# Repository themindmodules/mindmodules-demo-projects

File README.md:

# MindModules Demo Projects

Five complete example projects from [@themindmodules](https://instagram.com/themindmodules): PCB design,
STM32, Arduino, core electronics, a hobby build and a hackathon kit. Each folder is a self-contained project
with its own README, documentation, design files and BOM.

| # | Project | Type | What is inside |
|---|---|---|---|
| 01 | [stm32-adc-dma-datalogger](01-stm32-adc-dma-datalogger) | STM32 firmware | 4-channel ADC + DMA logger, CubeMX settings, timing maths, test plan |
| 02 | [arduino-plant-monitor](02-arduino-plant-monitor) | Arduino | Soil moisture + safe auto-watering, wiring, calibration, safety notes |
| 03 | [lm317-adjustable-supply](03-lm317-adjustable-supply) | **PCB** | KiCad schematic + PCB, gerbers, BOM, assembly and ordering guide |
| 04 | [nano-rgb-led-controller](04-nano-rgb-led-controller) | Hobby / mixed | 12 V RGB strip controller: schematic, perfboard guide, firmware |
| 05 | [hackathon-gridwatch](05-hackathon-gridwatch) | Hackathon | Energy anomaly detection demo, pitch, judge Q&A, 24 h plan |
| 06 | [stm32-rtc-low-power-logger](06-stm32-rtc-low-power-logger) | STM32 firmware | Stop 2 + RTC wake-up loop, VREFINT supply and temp maths, ring buffer, current budget model |
| 07 | [hobby-cable-tester](07-hobby-cable-tester) | Hobby / mixed | 8-wire tester with 595/165 scan: schematic, perfboard wiring table, firmware with testable logic |
| 08 | [pcb-lifepo4-4s-bms](08-pcb-lifepo4-4s-bms) | PCB | KiCad schematic and PCB, gerbers, TL431 balancer, LM393 cutoff, design notes, test plan. Topic suggested by Sujan Ghosh |
| 09 | [stm32-i2c-sensor-logger](09-stm32-i2c-sensor-logger) | STM32 firmware | Bus scan with device hints, LM75/TMP102 CSV logger, CubeMX settings, pull-up maths, test plan |
| 10 | [pcb-transistor-relay-driver](10-pcb-transistor-relay-driver) | PCB | BC337 low side relay drivers with flyback diodes and LEDs, base resistor maths, KiCad schematic, routed PCB and gerbers |
| 11 | [stm32-pwm-motor-speed-controller](11-stm32-pwm-motor-speed-controller) | STM32 firmware | STM32F411 + DRV8871, encoder on TIM2, 100 Hz PI loop with anti-windup, live tuning over UART, loop simulator |
| 12 | [hack-attendance-qr](12-hack-attendance-qr) | Hackathon | Rotating QR token, scan simulator, proxy and duplicate rules, self-test, dashboard, pitch and judge Q&A |

## Status

These are reference designs. The KiCad files pass ERC/DRC and the code compiles, but **no board here has been
fabricated or bench-tested**, and the hackathon demo runs on simulated data. Every README says exactly what was
and was not verified. Follow the test plans before trusting any design, and take care with anything that touches mains voltage.

## Want more?

Exclusive PCB designs, STM32 and Arduino projects, documentation, personal guidance, Q&A and doubt calls are
available to Inner Circle subscribers on Instagram: [@themindmodules](https://instagram.com/themindmodules).

## License

See `LICENSE.md` inside each project.

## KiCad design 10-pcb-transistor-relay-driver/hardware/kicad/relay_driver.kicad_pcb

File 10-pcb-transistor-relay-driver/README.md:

# Two Channel Transistor Relay Driver (5 V coil)

A small through-hole board that lets a microcontroller pin switch a 5 V relay. Each channel uses
an NPN transistor as a low side switch, a base resistor sized for both 5 V and 3.3 V logic,
a pull-down so the relay stays off while the controller boots, a flyback diode across the coil
and an LED that shows when the coil is powered. Two identical channels sit side by side.

> **Status:** the schematic passes KiCad ERC (0 issues) and the PCB passes DRC (0 violations,
> 0 unconnected). The exported netlist was checked against the intended connections, net by net.
> All component values come from hand calculations in `docs/design-notes.md`. The circuit was
> **not simulated** and the board has **not been built or tested on a bench yet**. Treat the first
> build as a prototype and follow `docs/assembly-and-test.md`.

## What it does

| Block | Parts per channel | Value |
|---|---|---|
| Switch | BC337 NPN in TO-92 | coil current about 71 mA, transistor fully saturated |
| Base drive | 470 ohm series resistor | about 8.9 mA from a 5 V pin, about 5.2 mA from a 3.3 V pin |
| Off by default | 10k base pull-down | relay stays off while the input floats |
| Coil protection | 1N4148 across the coil | collector clamps near 5.8 V when the coil turns off |
| Indicator | red LED with 1k | about 3 mA, lights while the coil is on |

## At a glance

| Item | Value |
|---|---|
| Coil supply | 5 V DC, about 150 mA with both relays on |
| Logic input | 3.3 V or 5 V, active high, about 5 to 9 mA per input |
| Relay | SRD-05VDC-SL-C (SPDT, COM, NC and NO brought out) |
| Contact limit on this board | **24 V DC, 3 A**. Low voltage only, never mains |
| Board | 64 x 76 mm, 2 layers, all through-hole, two M3 holes |
| Tools | KiCad 10 (project files included) |

## Connectors

| Connector | Pins |
|---|---|
| J3 screw terminal | +5V, GND (coil supply) |
| J4 pin header | 5V, IN1, IN2, GND (to the microcontroller) |
| J1, J2 screw terminals | COM, NC, NO for relay 1 and relay 2 |

The 5V pin on J4 is the same net as J3. Power the board from one of them, not two different supplies.

## Folder map

| Path | Contents |
|---|---|
| `hardware/kicad/` | KiCad project: `.kicad_pro`, `.kicad_sch`, `.kicad_pcb` |
| `hardware/gerbers/` | Gerbers, drill file and placement file |
| `hardware/docs/` | Schematic PDF, PCB PDF and SVG, top layer preview |
| `hardware/reports/` | DRC, ERC and netlist reports |
| `bom/bom.csv` | Bill of materials |
| `docs/design-notes.md` | How the driver works, every formula and why each value was picked |
| `docs/assembly-and-test.md` | Build order, test plan and a short example sketch |
| `docs/ordering-gerbers.md` | How to order the PCB |
| `tools/` | Python scripts that generate the schematic and PCB (rebuild with KiCad's Python) |

## Quick start

1. Read `docs/design-notes.md` so you know why the values are what they are.
2. Order the PCB from the files in `hardware/gerbers/` (see `docs/ordering-gerbers.md`) and buy the parts in `bom/bom.csv`.
3. Build and check it with `docs/assembly-and-test.md`. Test with a current limited 5 V supply first.

## Rebuild the design files

```sh
"<KiCad>/bin/python.exe" tools/build_relay.py <path-to-this-project>
sh tools/export.sh <path-to-this-project> relay_driver     # needs kicad-cli
```

`tools/router.py` is a small grid router that lays the signal tracks. The relay contact tracks are
placed by hand at 1.5 mm width.

## License

Personal and educational use for MindModules Inner Circle subscribers. See `LICENSE.md`.

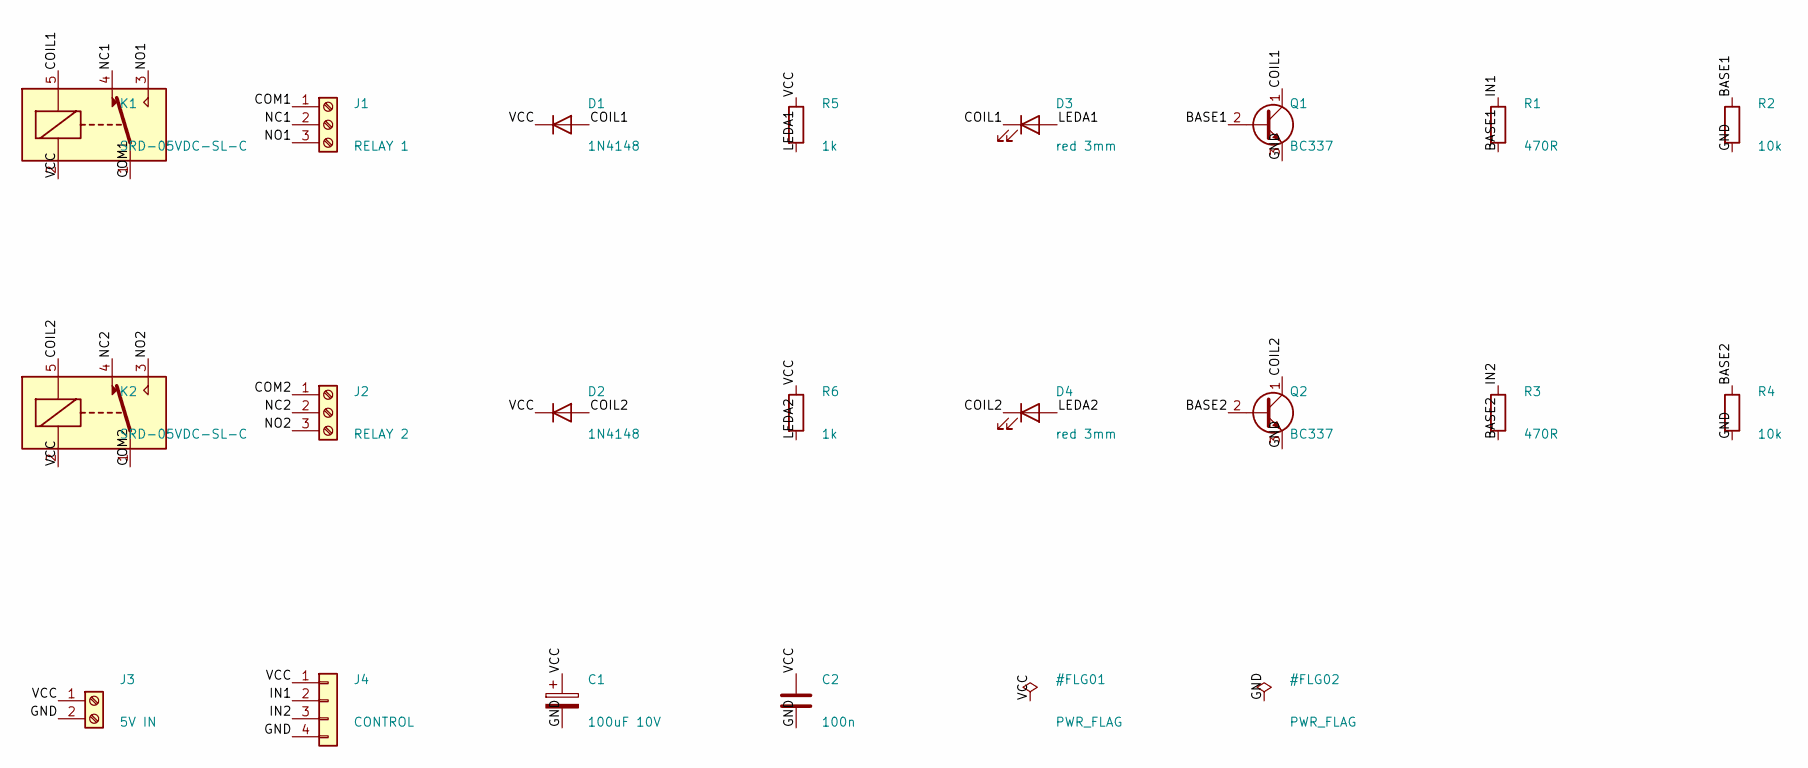
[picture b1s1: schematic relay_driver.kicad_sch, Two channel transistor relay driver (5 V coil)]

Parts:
C1: 100uF 10V; CP_Radial_D6.3mm_P2.50mm
C2: 100n; C_Disc_D5.0mm_W2.5mm_P5.00mm
D1, D2: 1N4148; D_DO-35_SOD27_P7.62mm_Horizontal
D3, D4: red 3mm; LED_D3.0mm
J1: RELAY 1; TerminalBlock_Phoenix_MKDS-1,5-3-5.08_1x03_P5.08mm_Horizont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
J2: RELAY 2; TerminalBlock_Phoenix_MKDS-1,5-3-5.08_1x03_P5.08mm_Horizont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
J3: 5V IN; TerminalBlock_Phoenix_MKDS-1,5-2-5.08_1x02_P5.08mm_Horizont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
J4: CONTROL; PinHeader_1x04_P2.54mm_Vertical
K1, K2: SRD-05VDC-SL-C; Relay_SPDT_SANYOU_SRD_Series_Form_C
Q1, Q2: BC337; TO-92_Inline_Wide
R1, R3: 470R; R_Axial_DIN0207_L6.3mm_D2.5mm_P7.62mm_Horizontal
R2, R4: 10k; R_Axial_DIN0207_L6.3mm_D2.5mm_P7.62mm_Horizontal
R5, R6: 1k; R_Axial_DIN0207_L6.3mm_D2.5mm_P7.62mm_Horizontal

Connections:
BASE1: Q1.2 (B), R1.2, R2.1
BASE2: Q2.2 (B), R3.2, R4.1
COIL1: D1.2 (A), D3.1 (K), K1.5, Q1.1 (C)
COIL2: D2.2 (A), D4.1 (K), K2.5, Q2.1 (C)
COM1: J1.1, K1.1
COM2: J2.1, K2.1
GND: C1.2, C2.2, J3.2, J4.4, Q1.3 (E), Q2.3 (E), R2.2, R4.2
IN1: J4.2, R1.1
IN2: J4.3, R3.1
LEDA1: D3.2 (A), R5.2
LEDA2: D4.2 (A), R6.2
NC1: J1.2, K1.4
NC2: J2.2, K2.4
NO1: J1.3, K1.3
NO2: J2.3, K2.3
VCC: C1.1, C2.1, D1.1 (K), D2.1 (K), J3.1, J4.1, K1.2, K2.2, R5.1, R6.1

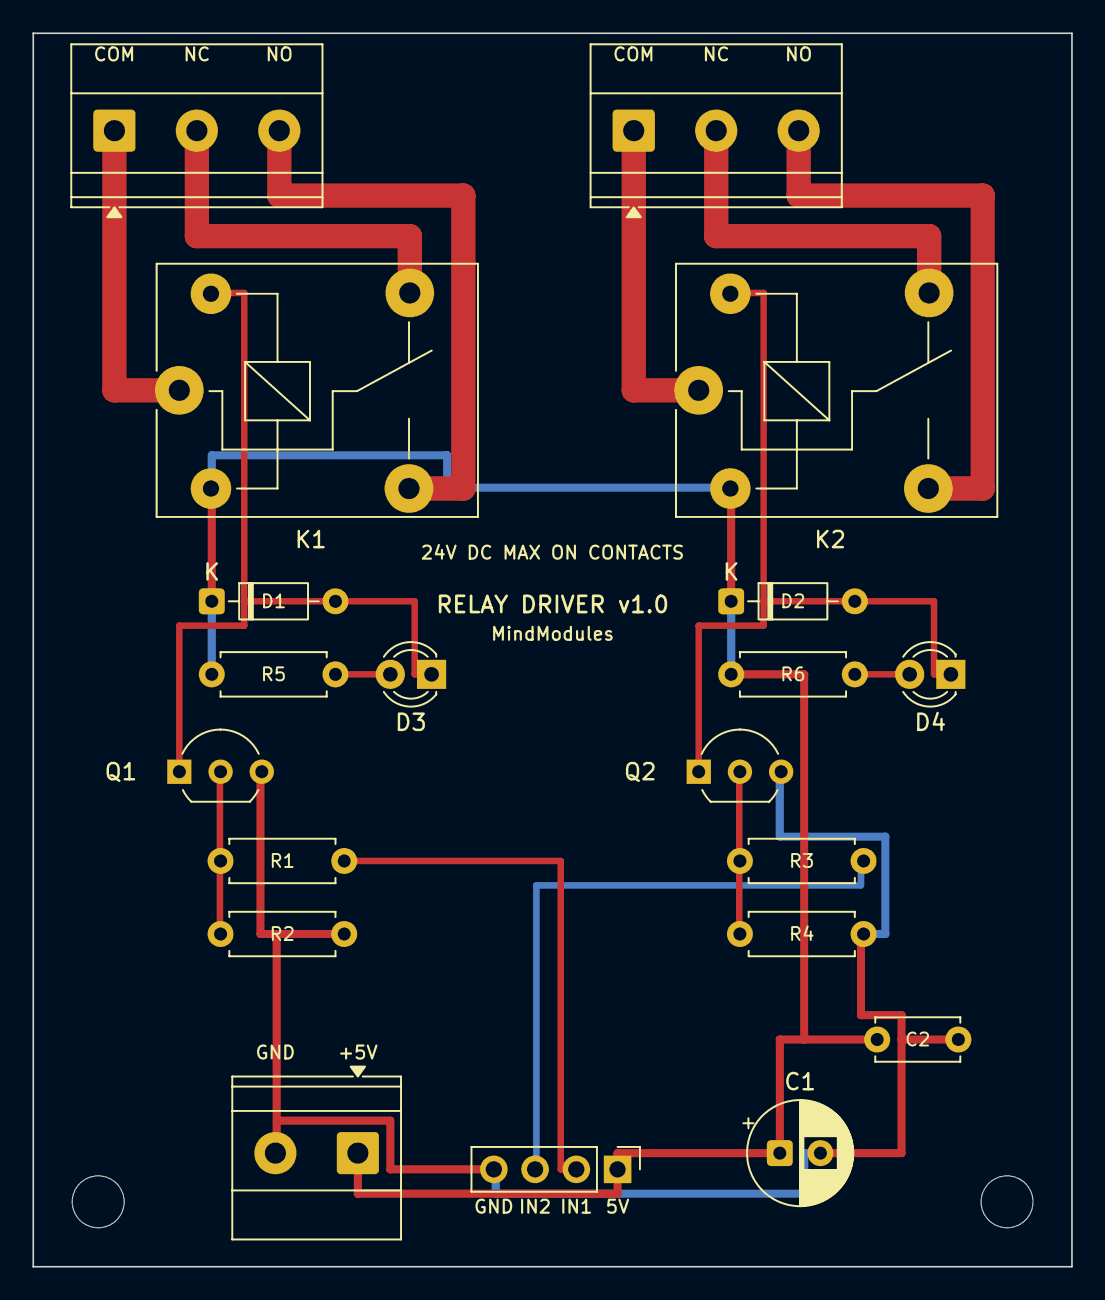
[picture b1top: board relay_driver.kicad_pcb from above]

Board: 2 copper layers, 64.0 x 76.0 mm, 22 parts (0 on the bottom side), 16 nets.

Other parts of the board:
H: MountingHole_3.2mm_M3
H#2: MountingHole_3.2mm_M3

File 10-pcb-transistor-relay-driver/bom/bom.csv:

"Refs","Value","Footprint","Qty","DNP"
"C1","100uF 10V","Capacitor_THT:CP_Radial_D6.3mm_P2.50mm","1",""
"C2","100n","Capacitor_THT:C_Disc_D5.0mm_W2.5mm_P5.00mm","1",""
"D1","1N4148","Diode_THT:D_DO-35_SOD27_P7.62mm_Horizontal","1",""
"D2","1N4148","Diode_THT:D_DO-35_SOD27_P7.62mm_Horizontal","1",""
"D3","red 3mm","LED_THT:LED_D3.0mm","1",""
"D4","red 3mm","LED_THT:LED_D3.0mm","1",""
"J1","RELAY 1","TerminalBlock_Phoenix:TerminalBlock_Phoenix_MKDS-1,5-3-5.08_1x03_P5.08mm_Horizontal","1",""
"J2","RELAY 2","TerminalBlock_Phoenix:TerminalBlock_Phoenix_MKDS-1,5-3-5.08_1x03_P5.08mm_Horizontal","1",""
"J3","5V IN","TerminalBlock_Phoenix:TerminalBlock_Phoenix_MKDS-1,5-2-5.08_1x02_P5.08mm_Horizontal","1",""
"J4","CONTROL","Connector_PinHeader_2.54mm:PinHeader_1x04_P2.54mm_Vertical","1",""
"K1","SRD-05VDC-SL-C","Relay_THT:Relay_SPDT_SANYOU_SRD_Series_Form_C","1",""
"K2","SRD-05VDC-SL-C","Relay_THT:Relay_SPDT_SANYOU_SRD_Series_Form_C","1",""
"Q1","BC337","Package_TO_SOT_THT:TO-92_Inline_Wide","1",""
"Q2","BC337","Package_TO_SOT_THT:TO-92_Inline_Wide","1",""
"R1","470R","Resistor_THT:R_Axial_DIN0207_L6.3mm_D2.5mm_P7.62mm_Horizontal","1",""
"R2","10k","Resistor_THT:R_Axial_DIN0207_L6.3mm_D2.5mm_P7.62mm_Horizontal","1",""
"R3","470R","Resistor_THT:R_Axial_DIN0207_L6.3mm_D2.5mm_P7.62mm_Horizontal","1",""
"R4","10k","Resistor_THT:R_Axial_DIN0207_L6.3mm_D2.5mm_P7.62mm_Horizontal","1",""
"R5","1k","Resistor_THT:R_Axial_DIN0207_L6.3mm_D2.5mm_P7.62mm_Horizontal","1",""
"R6","1k","Resistor_THT:R_Axial_DIN0207_L6.3mm_D2.5mm_P7.62mm_Horizontal","1",""

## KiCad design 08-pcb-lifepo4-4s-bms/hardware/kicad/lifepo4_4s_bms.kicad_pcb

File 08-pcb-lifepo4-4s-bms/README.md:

# 4S LiFePO4 BMS: Cell Balancer and Load Protection Board

A through-hole battery management board for a 4 cell LiFePO4 pack (also called LFP or IFP cells,
12.8 V nominal, 14.6 V full). It does two jobs: it balances each cell at the top of charge, and it
disconnects the load on pack under-voltage and on over-current.

**Topic suggested by Sujan Ghosh** on the @themindmodules Instagram channel. Thanks Sujan.

> **Status:** the schematic passes KiCad ERC (0 issues) and the PCB passes DRC (0 violations,
> 0 unconnected), and the exported netlist matches the intended connections. All thresholds were
> calculated by hand and are listed in `docs/design-notes.md`. The circuit was **not simulated**
> and the board has **not been built or tested on a bench**. Treat the first build as a prototype,
> and read `docs/limits-and-safety.md` before connecting a real battery.

## What it does

| Function | How | Value |
|---|---|---|
| Cell balancing | One TL431 shunt per cell, starts bleeding through an 18 ohm resistor | starts at 3.60 V per cell, about 60 to 85 mA |
| Pack under-voltage cutoff | LM393 comparator watches the pack voltage and switches off a logic-level MOSFET | cuts at about 11.04 V (2.76 V per cell), reconnects at about 11.21 V |
| Over-current cutoff | 20 milliohm shunt, second comparator | trips at about 10 A |
| Load switch | IRLZ44N in the negative (low side) line | charging still flows through its body diode |

## What it does not do

It has no over-charge disconnect and no per cell under-voltage cutoff. It needs a proper
CC/CV LiFePO4 charger set to 14.4 V. The full list is in `docs/limits-and-safety.md`.

## At a glance

| Item | Value |
|---|---|
| Cells | 4 in series, LiFePO4 only (not Li-ion, not lead acid) |
| Pack voltage | 10 V to 14.6 V |
| Continuous current | **5 A** (copper width and shunt power), trips at about 10 A |
| Board | 100 x 94 mm, 2 layers, through-hole, four M3 holes |
| Idle drain | roughly 2.6 mA from the whole pack, so do not store a pack on the board |
| Tools | KiCad 10 (project files included) |

## Folder map

| Path | Contents |
|---|---|
| `hardware/kicad/` | KiCad project: `.kicad_pro`, `.kicad_sch`, `.kicad_pcb` |
| `hardware/gerbers/` | Gerbers, drill file and placement file |
| `hardware/docs/` | Schematic PDF, PCB PDF and SVG, preview images |
| `hardware/reports/` | DRC, ERC and netlist reports |
| `bom/bom.csv` | Bill of materials |
| `docs/design-notes.md` | How each block works, every formula and threshold |
| `docs/limits-and-safety.md` | What the board cannot protect against, and LiFePO4 handling rules |
| `docs/assembly-and-test.md` | Build order and a bench test plan using a variable supply |
| `tools/` | Python scripts that generate the schematic and PCB (rebuild with KiCad's Python) |

## Quick start

1. Read `docs/limits-and-safety.md` first.
2. Read `docs/design-notes.md` so you know why the values are what they are.
3. Order the PCB from the files in `hardware/gerbers/` and buy the parts in `bom/bom.csv`.
4. Build and test with `docs/assembly-and-test.md`. Test on a bench supply before any real cells.

## Rebuild the design files

```sh
"<KiCad>/bin/python.exe" tools/build_bms.py <path-to-this-repo>
sh tools/export.sh <path-to-this-repo> lifepo4_4s_bms     # needs kicad-cli
```

`tools/router.py` is a small grid router used to lay the tracks. The power tracks (pack positive,
shunt, load return) are placed by hand at 2 mm width.

## License

Personal and educational use for MindModules Inner Circle subscribers. See `LICENSE.md`.

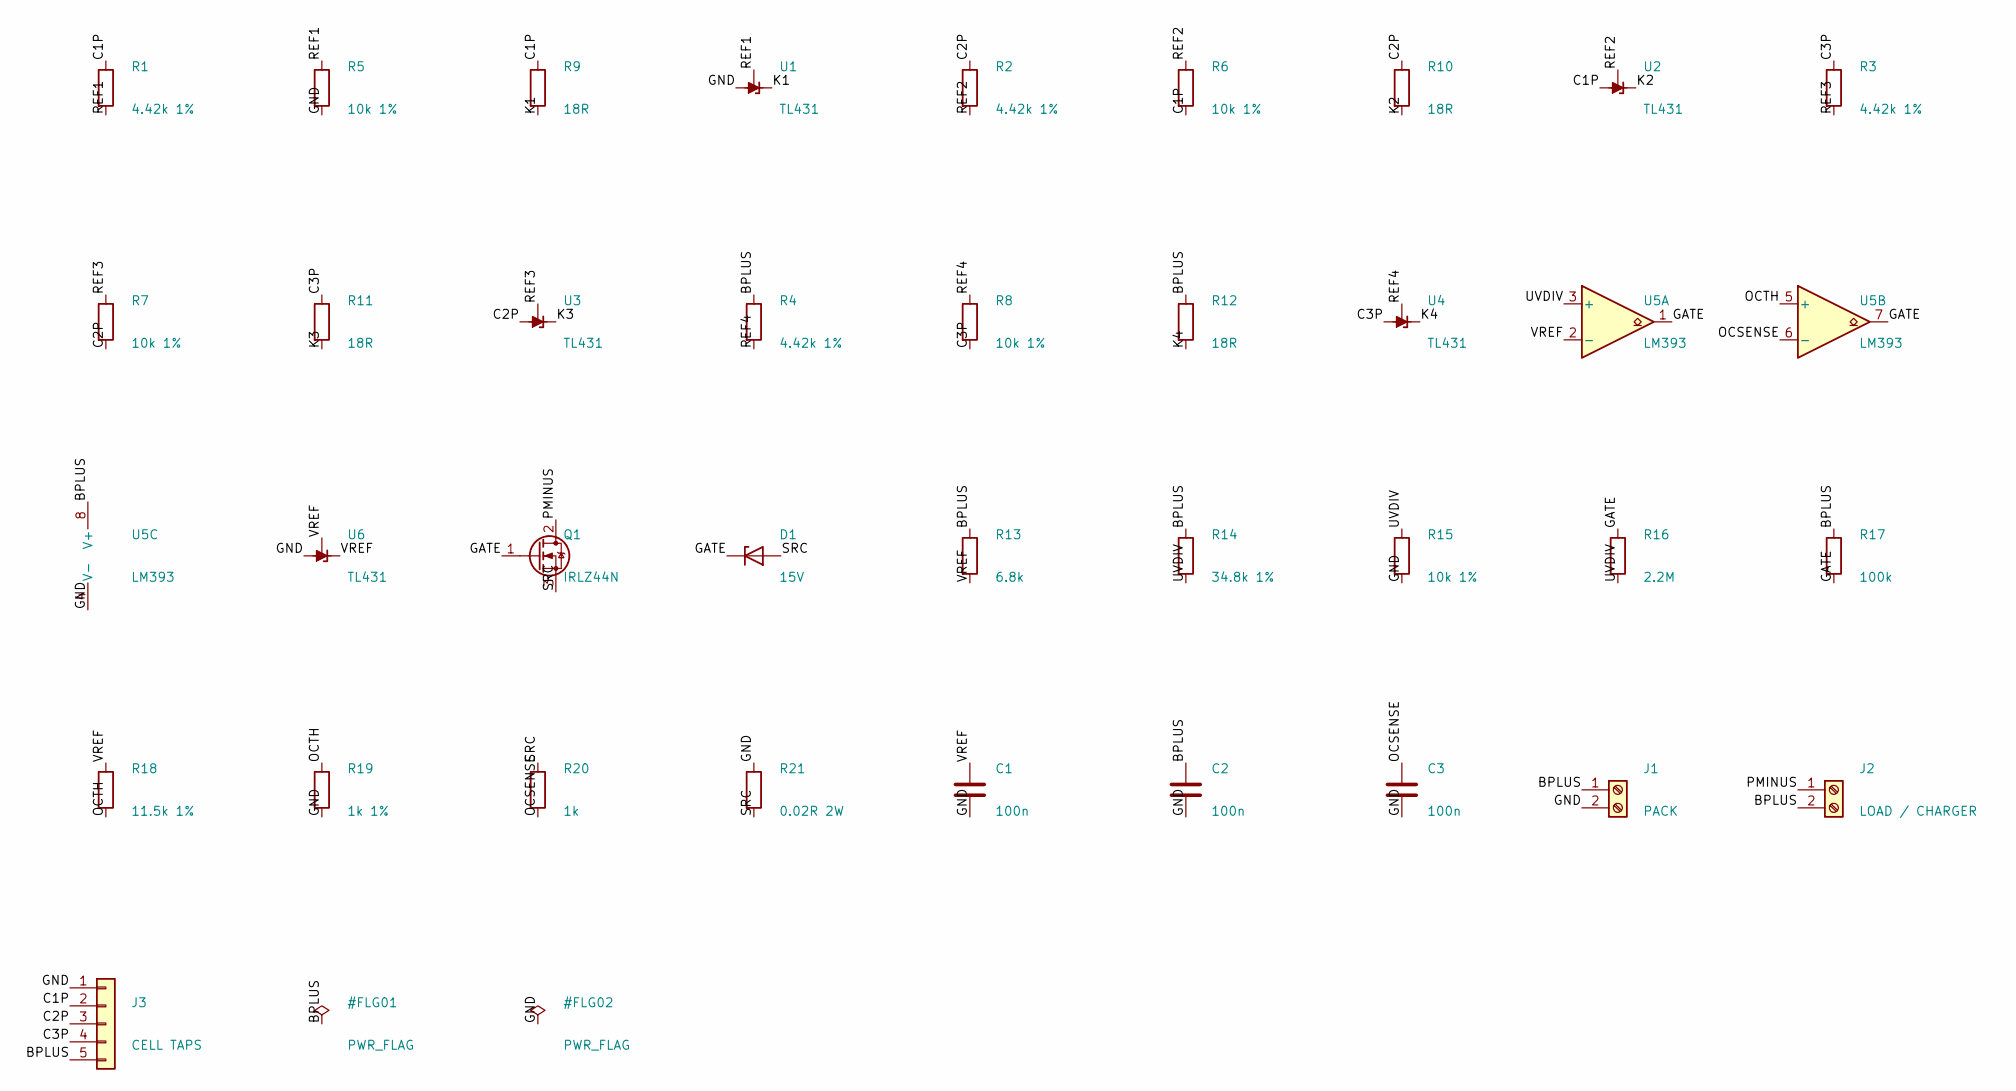
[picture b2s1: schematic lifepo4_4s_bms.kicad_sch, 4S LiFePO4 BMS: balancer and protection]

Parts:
C1, C2, C3: 100n; C_Disc_D5.0mm_W2.5mm_P5.00mm
D1: 15V; D_DO-41_SOD81_P10.16mm_Horizontal
J1: PACK; TerminalBlock_Phoenix_MKDS-1,5-2-5.08_1x02_P5.08mm_Horizont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
J2: LOAD / CHARGER; TerminalBlock_Phoenix_MKDS-1,5-2-5.08_1x02_P5.08mm_Horizont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
J3: CELL TAPS; PinHeader_1x05_P2.54mm_Vertical
Q1: IRLZ44N; TO-220-3_Vertical
R1, R2, R3, R4: 4.42k 1%; R_Axial_DIN0207_L6.3mm_D2.5mm_P7.62mm_Horizontal
R5, R6, R7, R8, R15: 10k 1%; R_Axial_DIN0207_L6.3mm_D2.5mm_P7.62mm_Horizontal
R9, R10, R11, R12: 18R; R_Axial_DIN0207_L6.3mm_D2.5mm_P7.62mm_Horizontal
R13: 6.8k; R_Axial_DIN0207_L6.3mm_D2.5mm_P7.62mm_Horizontal
R14: 34.8k 1%; R_Axial_DIN0207_L6.3mm_D2.5mm_P7.62mm_Horizontal
R16: 2.2M; R_Axial_DIN0207_L6.3mm_D2.5mm_P7.62mm_Horizontal
R17: 100k; R_Axial_DIN0207_L6.3mm_D2.5mm_P7.62mm_Horizontal
R18: 11.5k 1%; R_Axial_DIN0207_L6.3mm_D2.5mm_P7.62mm_Horizontal
R19: 1k 1%; R_Axial_DIN0207_L6.3mm_D2.5mm_P7.62mm_Horizontal
R20: 1k; R_Axial_DIN0207_L6.3mm_D2.5mm_P7.62mm_Horizontal
R21: 0.02R 2W; R_Axial_DIN0414_L11.9mm_D4.5mm_P15.24mm_Horizontal
U1, U2, U3, U4, U6: TL431; TO-92_Inline
U5: LM393; DIP-8_W7.62mm

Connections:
BPLUS: C2.1, J1.1, J2.2, J3.5, R4.1, R12.1, R13.1, R14.1, R17.1, U5.8 (V+)
C1P: J3.2, R1.1, R6.2, R9.1, U2.2 (A)
C2P: J3.3, R2.1, R7.2, R10.1, U3.2 (A)
C3P: J3.4, R3.1, R8.2, R11.1, U4.2 (A)
GATE: D1.1 (K), Q1.1 (G), R16.1, R17.2, U5.1, U5.7
GND: C1.2, C2.2, C3.2, J1.2, J3.1, R5.2, R15.2, R19.2, R21.1, U1.2 (A), U5.4 (V-), U6.2 (A)
K1: R9.2, U1.3 (K)
K2: R10.2, U2.3 (K)
K3: R11.2, U3.3 (K)
K4: R12.2, U4.3 (K)
OCSENSE: C3.1, R20.2, U5.6 (-)
OCTH: R18.2, R19.1, U5.5 (+)
PMINUS: J2.1, Q1.2 (D)
REF1: R1.2, R5.1, U1.1 (REF)
REF2: R2.2, R6.1, U2.1 (REF)
REF3: R3.2, R7.1, U3.1 (REF)
REF4: R4.2, R8.1, U4.1 (REF)
SRC: D1.2 (A), Q1.3 (S), R20.1, R21.2
UVDIV: R14.2, R15.1, R16.2, U5.3 (+)
VREF: C1.1, R13.2, R18.1, U5.2 (-), U6.1 (REF), U6.3 (K)

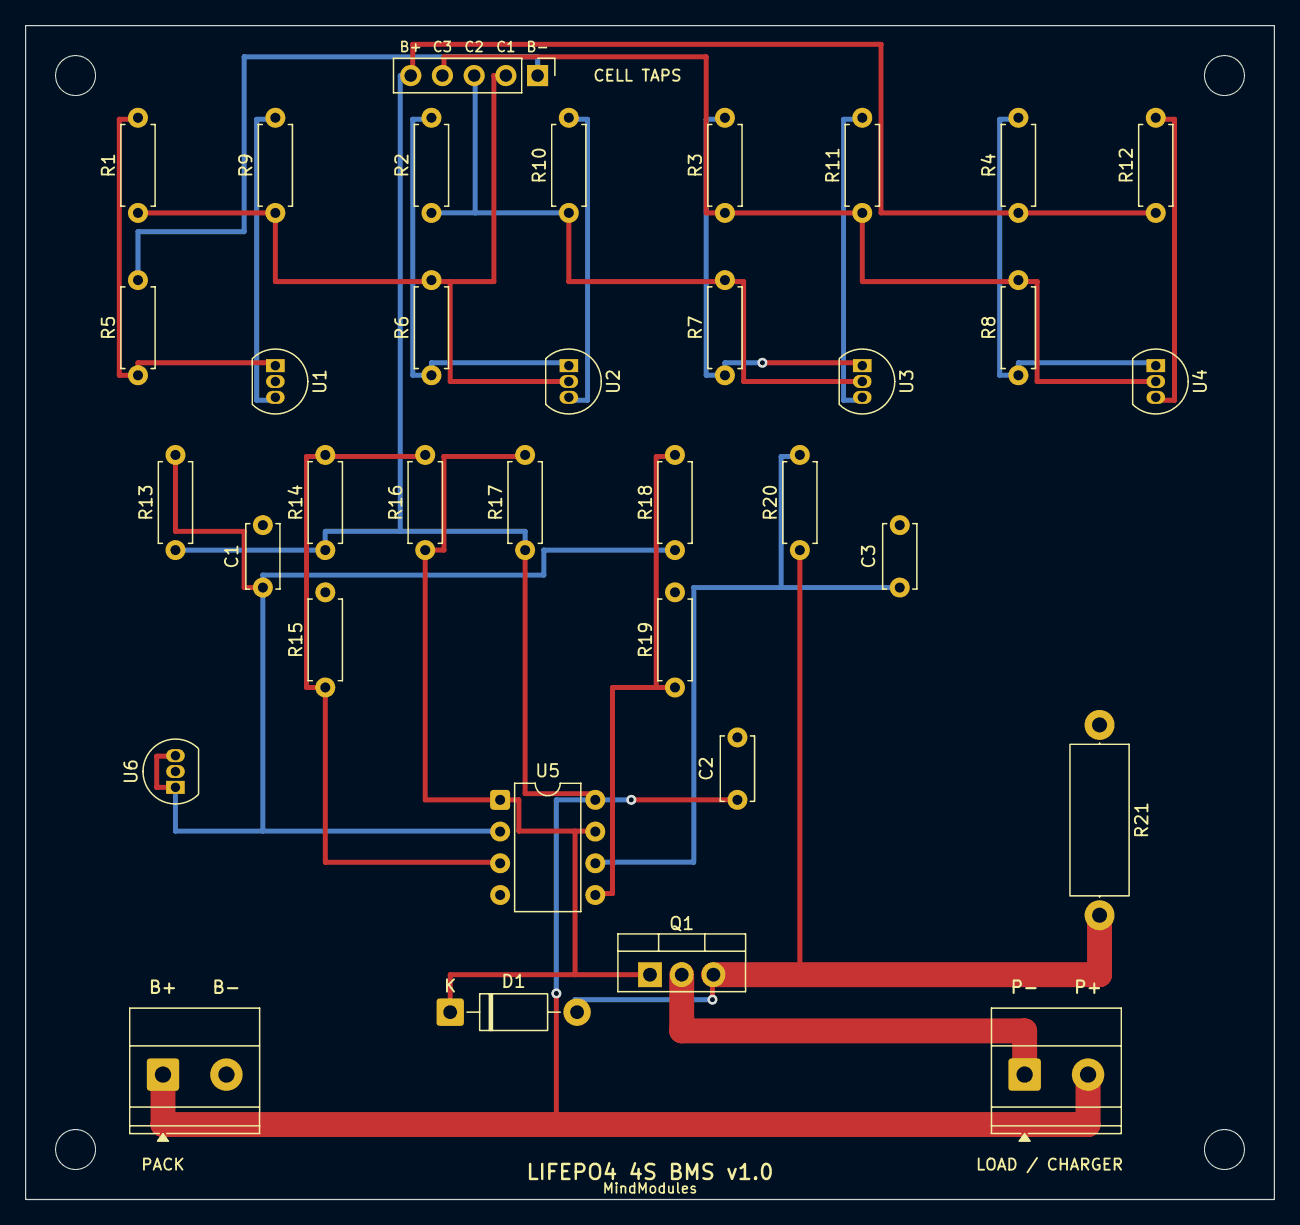
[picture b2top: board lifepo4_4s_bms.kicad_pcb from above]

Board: 2 copper layers, 100.0 x 94.0 mm, 39 parts (0 on the bottom side), 20 nets.

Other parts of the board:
H: MountingHole_3.2mm_M3
H#2, H#3, H#4: MountingHole_3.2mm_M3

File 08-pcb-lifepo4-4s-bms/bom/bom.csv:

"Refs","Value","Footprint","Qty","DNP"
"C1","100n","Capacitor_THT:C_Disc_D5.0mm_W2.5mm_P5.00mm","1",""
"C2","100n","Capacitor_THT:C_Disc_D5.0mm_W2.5mm_P5.00mm","1",""
"C3","100n","Capacitor_THT:C_Disc_D5.0mm_W2.5mm_P5.00mm","1",""
"D1","15V","Diode_THT:D_DO-41_SOD81_P10.16mm_Horizontal","1",""
"J1","PACK","TerminalBlock_Phoenix:TerminalBlock_Phoenix_MKDS-1,5-2-5.08_1x02_P5.08mm_Horizontal","1",""
"J2","LOAD / CHARGER","TerminalBlock_Phoenix:TerminalBlock_Phoenix_MKDS-1,5-2-5.08_1x02_P5.08mm_Horizontal","1",""
"J3","CELL TAPS","Connector_PinHeader_2.54mm:PinHeader_1x05_P2.54mm_Vertical","1",""
"Q1","IRLZ44N","Package_TO_SOT_THT:TO-220-3_Vertical","1",""
"R1","4.42k 1%","Resistor_THT:R_Axial_DIN0207_L6.3mm_D2.5mm_P7.62mm_Horizontal","1",""
"R2","4.42k 1%","Resistor_THT:R_Axial_DIN0207_L6.3mm_D2.5mm_P7.62mm_Horizontal","1",""
"R3","4.42k 1%","Resistor_THT:R_Axial_DIN0207_L6.3mm_D2.5mm_P7.62mm_Horizontal","1",""
"R4","4.42k 1%","Resistor_THT:R_Axial_DIN0207_L6.3mm_D2.5mm_P7.62mm_Horizontal","1",""
"R5","10k 1%","Resistor_THT:R_Axial_DIN0207_L6.3mm_D2.5mm_P7.62mm_Horizontal","1",""
"R6","10k 1%","Resistor_THT:R_Axial_DIN0207_L6.3mm_D2.5mm_P7.62mm_Horizontal","1",""
"R7","10k 1%","Resistor_THT:R_Axial_DIN0207_L6.3mm_D2.5mm_P7.62mm_Horizontal","1",""
"R8","10k 1%","Resistor_THT:R_Axial_DIN0207_L6.3mm_D2.5mm_P7.62mm_Horizontal","1",""
"R9","18R","Resistor_THT:R_Axial_DIN0207_L6.3mm_D2.5mm_P7.62mm_Horizontal","1",""
"R10","18R","Resistor_THT:R_Axial_DIN0207_L6.3mm_D2.5mm_P7.62mm_Horizontal","1",""
"R11","18R","Resistor_THT:R_Axial_DIN0207_L6.3mm_D2.5mm_P7.62mm_Horizontal","1",""
"R12","18R","Resistor_THT:R_Axial_DIN0207_L6.3mm_D2.5mm_P7.62mm_Horizontal","1",""
"R13","6.8k","Resistor_THT:R_Axial_DIN0207_L6.3mm_D2.5mm_P7.62mm_Horizontal","1",""
"R14","34.8k 1%","Resistor_THT:R_Axial_DIN0207_L6.3mm_D2.5mm_P7.62mm_Horizontal","1",""
"R15","10k 1%","Resistor_THT:R_Axial_DIN0207_L6.3mm_D2.5mm_P7.62mm_Horizontal","1",""
"R16","2.2M","Resistor_THT:R_Axial_DIN0207_L6.3mm_D2.5mm_P7.62mm_Horizontal","1",""
"R17","100k","Resistor_THT:R_Axial_DIN0207_L6.3mm_D2.5mm_P7.62mm_Horizontal","1",""
"R18","11.5k 1%","Resistor_THT:R_Axial_DIN0207_L6.3mm_D2.5mm_P7.62mm_Horizontal","1",""
"R19","1k 1%","Resistor_THT:R_Axial_DIN0207_L6.3mm_D2.5mm_P7.62mm_Horizontal","1",""
"R20","1k","Resistor_THT:R_Axial_DIN0207_L6.3mm_D2.5mm_P7.62mm_Horizontal","1",""
"R21","0.02R 2W","Resistor_THT:R_Axial_DIN0414_L11.9mm_D4.5mm_P15.24mm_Horizontal","1",""
"U1","TL431","Package_TO_SOT_THT:TO-92_Inline","1",""
"U2","TL431","Package_TO_SOT_THT:TO-92_Inline","1",""
"U3","TL431","Package_TO_SOT_THT:TO-92_Inline","1",""
"U4","TL431","Package_TO_SOT_THT:TO-92_Inline","1",""
"U5","LM393","Package_DIP:DIP-8_W7.62mm","1",""
"U6","TL431","Package_TO_SOT_THT:TO-92_Inline","1",""

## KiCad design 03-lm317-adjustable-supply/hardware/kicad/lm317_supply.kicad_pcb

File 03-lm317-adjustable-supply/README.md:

# LM317 Adjustable Bench Supply (1.25 V to about 11.8 V, up to 1 A)

A small through-hole linear regulator board: DC in (15-24 V), adjustable DC out with a trimmer.
It is the classic LM317 circuit done properly: input reverse-polarity diode, output-cap
discharge protection diode, and enough documentation to build, test and order it.

> **Status:** the schematic and PCB pass KiCad ERC (0 issues) and DRC (0 violations, 0 unconnected),
> and the exported netlist matches the intended connections. The board has **not** been fabricated
> or tested on a bench. Treat the first build as a prototype and follow `docs/assembly-and-test.md`,
> starting with a current-limited supply.

## At a glance

| Item | Value |
|---|---|
| Input | 15-24 V DC (needs at least Vout + about 3.2 V: 2.5 V regulator dropout + 0.7 V diode) |
| Output | 1.25 V to about 11.8 V, set by the trimmer |
| Max current | **1 A** (limited by D1, the 1N4007) and needs a heatsink at higher dissipation |
| Board | 66 x 38 mm, 2 layers, through-hole, two M3 holes |
| Tools | KiCad 10 (project files included) |

## Folder map

| Path | Contents |
|---|---|
| `hardware/kicad/` | KiCad project: `.kicad_pro`, `.kicad_sch`, `.kicad_pcb` |
| `hardware/gerbers/` | Gerbers + drill file, ready to upload to a PCB fab |
| `hardware/docs/` | Schematic PDF, PCB PDF and SVG, preview images |
| `hardware/reports/` | DRC, ERC and netlist reports |
| `bom/bom.csv` | Bill of materials |
| `docs/design-notes.md` | Formulas, thermal limits, why each part is there |
| `docs/assembly-and-test.md` | Build order and a test plan with expected readings |
| `docs/ordering-gerbers.md` | How to order the board |
| `tools/` | Python scripts that generated the schematic/PCB (rebuild with KiCad's Python) |

## Quick start

1. Read `docs/design-notes.md` (5 minutes) so you know the limits.
2. Order the PCB using `docs/ordering-gerbers.md`, buy parts from `bom/bom.csv`.
3. Build and test with `docs/assembly-and-test.md`.

## Rebuild the design files

```sh
"<KiCad>/bin/python.exe" tools/build_lm317.py <path-to-this-repo>
sh tools/export.sh <path-to-this-repo> lm317_supply     # needs kicad-cli
```

## License

Personal and educational use for MindModules Inner Circle subscribers. See `LICENSE.md`.

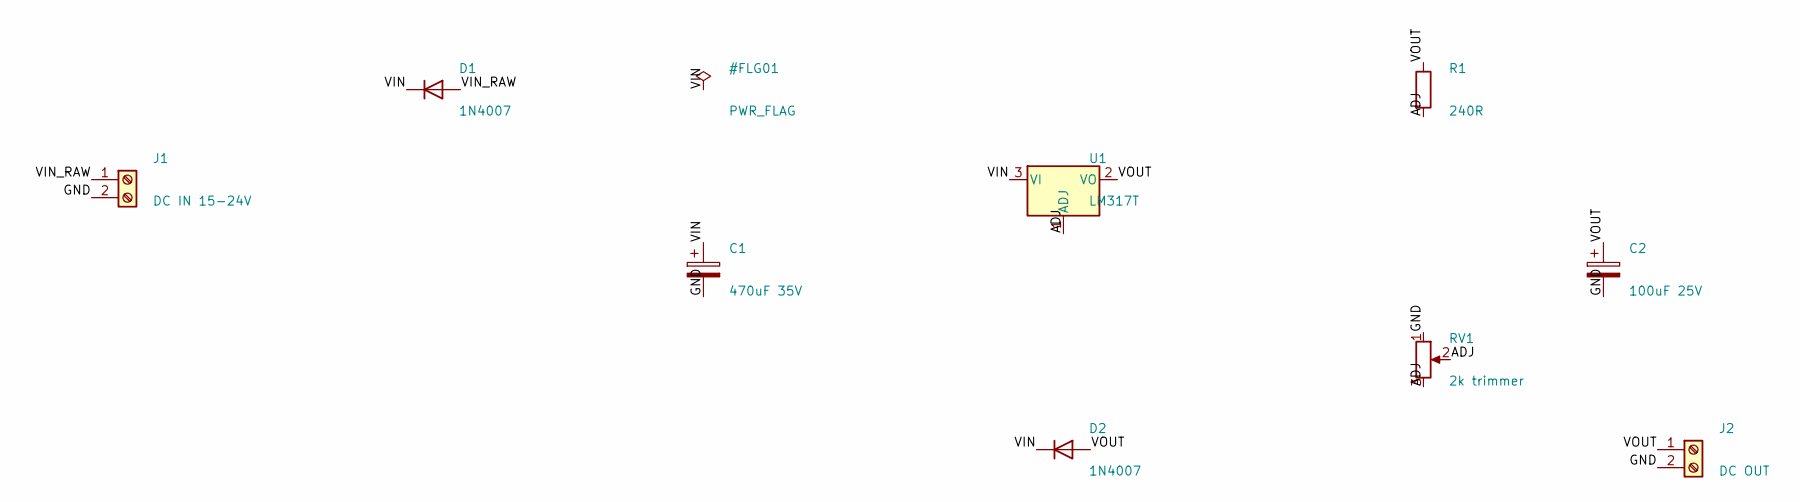
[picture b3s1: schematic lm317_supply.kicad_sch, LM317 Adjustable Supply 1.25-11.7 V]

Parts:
C1: 470uF 35V; CP_Radial_D8.0mm_P3.50mm
C2: 100uF 25V; CP_Radial_D6.3mm_P2.50mm
D1: 1N4007; D_DO-41_SOD81_P10.16mm_Horizontal
D2: 1N4007; D_DO-41_SOD81_P2.54mm_Vertical_CathodeUp
J1: DC IN 15-24V; TerminalBlock_Phoenix_MKDS-1,5-2-5.08_1x02_P5.08mm_Horizont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
J2: DC OUT; TerminalBlock_Phoenix_MKDS-1,5-2-5.08_1x02_P5.08mm_Horizont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
R1: 240R; R_Axial_DIN0207_L6.3mm_D2.5mm_P10.16mm_Horizontal
RV1: 2k trimmer; Potentiometer_Bourns_3296W_Vertical
U1: LM317T; TO-220-3_Vertical

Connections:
ADJ: R1.2, RV1.2, RV1.3, U1.1 (ADJ)
GND: C1.2, C2.2, J1.2, J2.2, RV1.1
VIN: C1.1, D1.1 (K), D2.1 (K), U1.3 (VI)
VIN_RAW: D1.2 (A), J1.1
VOUT: C2.1, D2.2 (A), J2.1, R1.1, U1.2 (VO)

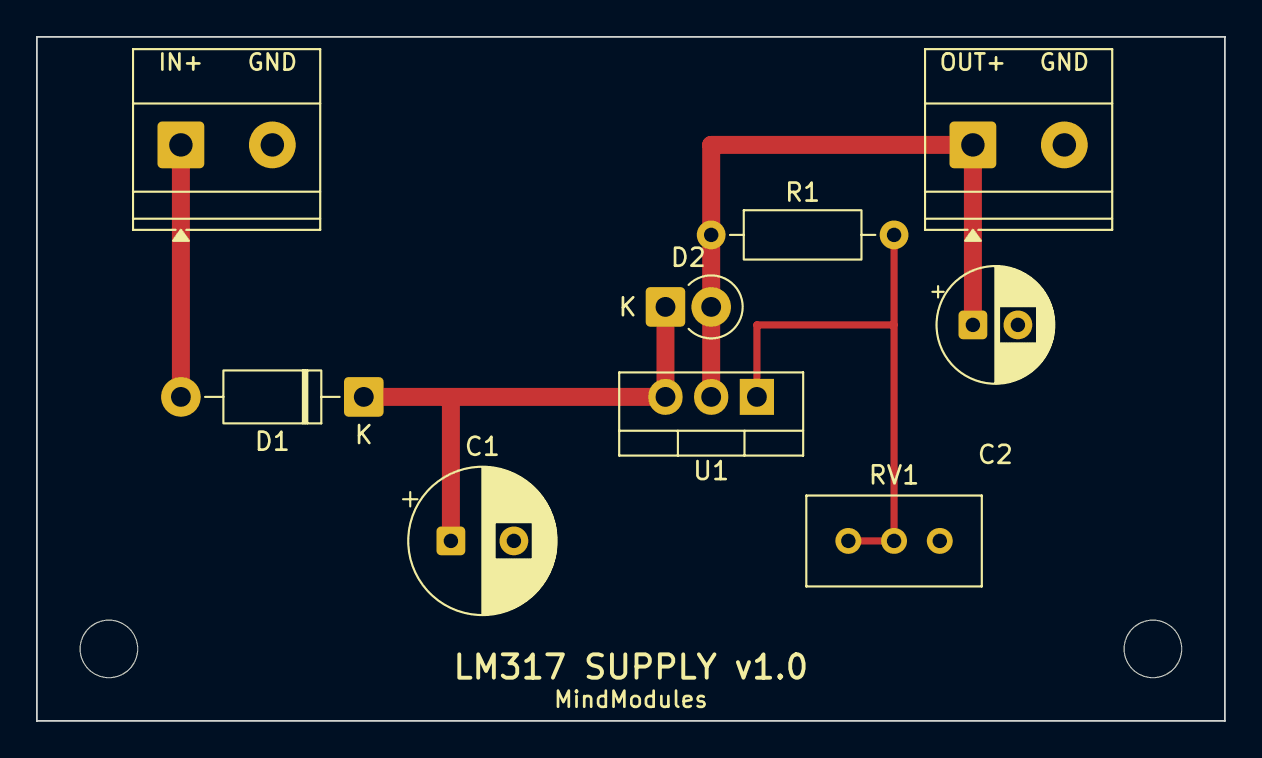
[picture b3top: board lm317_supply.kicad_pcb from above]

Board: 2 copper layers, 66.0 x 38.0 mm, 11 parts (0 on the bottom side), 5 nets.

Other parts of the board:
H: MountingHole_3.2mm_M3
H#2: MountingHole_3.2mm_M3

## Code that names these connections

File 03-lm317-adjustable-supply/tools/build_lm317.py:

"""Generate the LM317 adjustable supply: KiCad schematic + routed PCB.
Run with KiCad's bundled Python:  <KiCad>/bin/python.exe build_lm317.py <repo_root>
"""
import os
import sys

import pcbnew

sys.path.insert(0, os.path.dirname(os.path.abspath(__file__)))
import kigen

REPO = sys.argv[1]
NAME = "lm317_supply"
OUT = os.path.join(REPO, "hardware", "kicad")
os.makedirs(OUT, exist_ok=True)
FPLIB = r"D:\KICAD INSTALLATION\share\kicad\footprints"

TERM = "TerminalBlock_Phoenix:TerminalBlock_Phoenix_MKDS-1,5-2-5.08_1x02_P5.08mm_Horizontal"
TO220 = "Package_TO_SOT_THT:TO-220-3_Vertical"
D_H = "Diode_THT:D_DO-41_SOD81_P10.16mm_Horizontal"
D_V = "Diode_THT:D_DO-41_SOD81_P2.54mm_Vertical_CathodeUp"
CP8 = "Capacitor_THT:CP_Radial_D8.0mm_P3.50mm"
CP63 = "Capacitor_THT:CP_Radial_D6.3mm_P2.50mm"
R_H = "Resistor_THT:R_Axial_DIN0207_L6.3mm_D2.5mm_P10.16mm_Horizontal"
POT = "Potentiometer_THT:Potentiometer_Bourns_3296W_Vertical"

# ref, symbol, value, footprint, pin->net, schematic (x,y), pcb (x, y, rotation)
PARTS = [
    dict(ref="J1", lib="Connector:Screw_Terminal_01x02", value="DC IN 15-24V", fp=TERM,
         pins={"1": "VIN_RAW", "2": "GND"}, at=(45.72, 63.5), pcb=(8, 6, 0)),
    dict(ref="D1", lib="Device:D", value="1N4007", fp=D_H,
         pins={"1": "VIN", "2": "VIN_RAW"}, at=(88.9, 50.8), pcb=(18.16, 20, 180)),
    dict(ref="C1", lib="Device:C_Polarized", value="470uF 35V", fp=CP8,
         pins={"1": "VIN", "2": "GND"}, at=(127, 76.2), pcb=(23, 28, 0)),
    dict(ref="U1", lib="Regulator_Linear:LM317_TO-220", value="LM317T", fp=TO220,
         pins={"1": "ADJ", "2": "VOUT", "3": "VIN"}, at=(177.8, 63.5), pcb=(40, 20, 180)),
    dict(ref="D2", lib="Device:D", value="1N4007", fp=D_V,
         pins={"1": "VIN", "2": "VOUT"}, at=(177.8, 101.6), pcb=(34.92, 15, 0)),
    dict(ref="R1", lib="Device:R", value="240R", fp=R_H,
         pins={"1": "VOUT", "2": "ADJ"}, at=(228.6, 50.8), pcb=(37.46, 11, 0)),
    dict(ref="RV1", lib="Device:R_Potentiometer", value="2k trimmer", fp=POT,
         pins={"1": "GND", "2": "ADJ", "3": "ADJ"}, at=(228.6, 88.9), pcb=(50.16, 28, 0)),
    dict(ref="C2", lib="Device:C_Polarized", value="100uF 25V", fp=CP63,
         pins={"1": "VOUT", "2": "GND"}, at=(254, 76.2), pcb=(52, 16, 0)),
    dict(ref="J2", lib="Connector:Screw_Terminal_01x02", value="DC OUT", fp=TERM,
         pins={"1": "VOUT", "2": "GND"}, at=(266.7, 101.6), pcb=(52, 6, 0)),
    dict(ref="#FLG01", lib="power:PWR_FLAG", value="PWR_FLAG", fp="",
         pins={"1": "VIN"}, at=(127, 50.8), pcb=None),
]

# ---------------- schematic ----------------
kigen.generate_sch(os.path.join(OUT, NAME + ".kicad_sch"), NAME, "LM317 Adjustable Supply 1.25-11.7 V",
                   "A", PARTS, "Demo project for MindModules Inner Circle")
kigen.write_project(os.path.join(OUT, NAME + ".kicad_pro"), NAME)

# ---------------- PCB ----------------
OX, OY = 100.0, 80.0
W, H = 66.0, 38.0
FM = pcbnew.FromMM


def P(x, y):
    return pcbnew.VECTOR2I(FM(OX + x), FM(OY + y))


board = pcbnew.BOARD()
nets = {}
for n in sorted({v for p in PARTS for v in p["pins"].values()}):
    ni = pcbnew.NETINFO_ITEM(board, n)
    board.Add(ni)
    nets[n] = ni

origins = {}
for p in PARTS:
    if p["pcb"] is None:
        continue
    lib, name = p["fp"].split(":")
    fp = pcbnew.FootprintLoad(os.path.join(FPLIB, lib + ".pretty"), name)
    fp.SetReference(p["ref"])
    fp.SetValue(p["value"])
    x, y, rot = p["pcb"]
    fp.SetPosition(P(x, y))
    if rot:
        fp.SetOrientationDegrees(rot)
    for pad in fp.Pads():
        net = p["pins"].get(pad.GetNumber())
        if net:
            pad.SetNet(nets[net])
    fp.Value().SetVisible(False)
    if p["ref"] in ("J1", "J2"):
        fp.Reference().SetVisible(False)   # terminals are labelled by silk text instead
    if p["ref"] == "C2":
        fp.Reference().SetPosition(P(x + 1.25, y + 7.2))
    board.Add(fp)
    origins[p["ref"]] = fp


def pad(ref, num):
    for pd in origins[ref].Pads():
        if pd.GetNumber() == str(num):
            pos = pd.GetPosition()
            return (round(pcbnew.ToMM(pos.x) - OX, 3), round(pcbnew.ToMM(pos.y) - OY, 3))
    raise KeyError((ref, num))


def track(net, pts, w):
    for a, b in zip(pts, pts[1:]):
        t = pcbnew.PCB_TRACK(board)
        t.SetStart(P(*a))
        t.SetEnd(P(*b))
        t.SetWidth(FM(w))
        t.SetLayer(pcbnew.F_Cu)
        t.SetNet(nets[net])
        board.Add(t)


def line(a, b, layer, width):
    s = pcbnew.PCB_SHAPE(board)
    s.SetShape(pcbnew.SHAPE_T_SEGMENT)
    s.SetStart(P(*a))
    s.SetEnd(P(*b))
    s.SetLayer(layer)
    s.SetWidth(FM(width))
    board.Add(s)


# board outline
for a, b in [((0, 0), (W, 0)), ((W, 0), (W, H)), ((W, H), (0, H)), ((0, H), (0, 0))]:
    line(a, b, pcbnew.Edge_Cuts, 0.1)

# mounting holes
for hx, hy in [(4, H - 4), (W - 4, H - 4)]:
    mh = pcbnew.FootprintLoad(os.path.join(FPLIB, "MountingHole.pretty"), "MountingHole_3.2mm_M3")
    mh.SetReference("H")
    mh.Reference().SetVisible(False)
    mh.Value().SetVisible(False)
    mh.SetPosition(P(hx, hy))
    board.Add(mh)

# routing (all on F.Cu, GND is a pour on B.Cu)
PW, SG = 1.0, 0.4
track("VIN_RAW", [pad("J1", 1), pad("D1", 2)], PW)
track("VIN", [pad("D1", 1), pad("U1", 3)], PW)
track("VIN", [(23, 20), pad("C1", 1)], PW)
track("VIN", [pad("D2", 1), (pad("D2", 1)[0], 20)], PW)
track("VOUT", [pad("U1", 2), (pad("U1", 2)[0], 6), pad("J2", 1)], PW)
track("VOUT", [pad("J2", 1), pad("C2", 1)], PW)
adj_x = pad("R1", 2)[0]
track("ADJ", [pad("U1", 1), (pad("U1", 1)[0], 16), (adj_x, 16)], SG)
track("ADJ", [pad("R1", 2), (adj_x, 28), pad("RV1", 2)], SG)
track("ADJ", [pad("RV1", 2), pad("RV1", 3)], SG)

# GND pour on B.Cu
z = pcbnew.ZONE(board)
z.SetLayer(pcbnew.B_Cu)
z.SetNet(nets["GND"])
ol = z.Outline()
ol.NewOutline()
for cx, cy in [(0.5, 0.5), (W - 0.5, 0.5), (W - 0.5, H - 0.5), (0.5, H - 0.5)]:
    v = P(cx, cy)
    ol.Append(v.x, v.y)
z.SetMinThickness(FM(0.25))
z.SetLocalClearance(FM(0.4))
z.SetPadConnection(pcbnew.ZONE_CONNECTION_THERMAL)
board.Add(z)
pcbnew.ZONE_FILLER(board).Fill(board.Zones())


def text(s, x, y, size=1.2, layer=pcbnew.F_SilkS):
    t = pcbnew.PCB_TEXT(board)
    t.SetText(s)
    t.SetPosition(P(x, y))
    t.SetLayer(layer)
    t.SetTextSize(pcbnew.VECTOR2I(FM(size), FM(size)))
    t.SetTextThickness(FM(size / 6))
    board.Add(t)


text("LM317 SUPPLY v1.0", 33, H - 3, 1.3)
text("MindModules", 33, H - 1.2, 0.9)
text("IN+", 8, 1.4, 0.9)
text("GND", 13.08, 1.4, 0.9)
text("OUT+", 52, 1.4, 0.9)
text("GND", 57.08, 1.4, 0.9)

pcb_path = os.path.join(OUT, NAME + ".kicad_pcb")
board.Save(pcb_path)
print("saved", pcb_path)
